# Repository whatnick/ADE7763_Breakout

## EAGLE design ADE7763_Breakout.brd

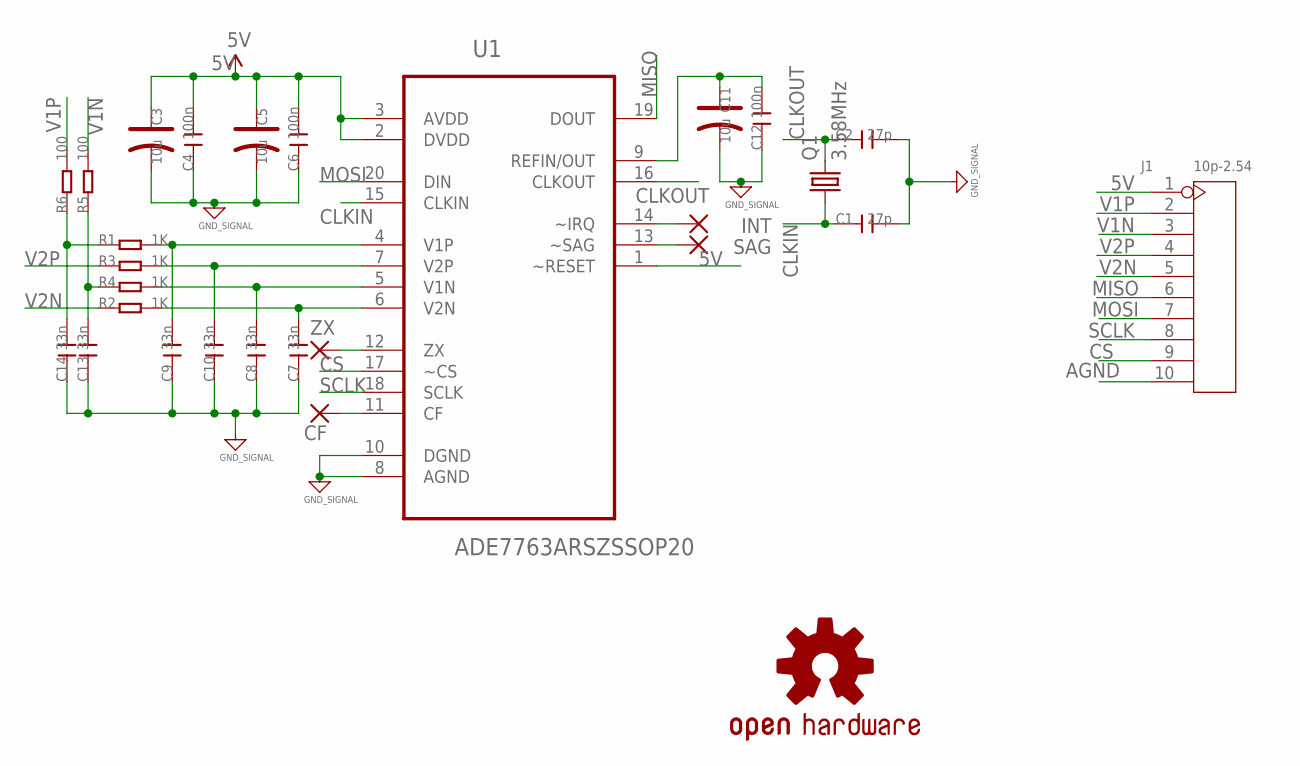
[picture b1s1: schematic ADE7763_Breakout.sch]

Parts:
C1, C2: 27p; C0603
C3, C5, C11: 10u; AVX-A
C4, C6, C12: 100n; C0603
C7, C8, C9, C10, C13, C14: 33n; C0603
CF: WIREPADSMD1,27-254; SMD1,27-2,54
INT: WIREPADSMD1,27-254; SMD1,27-2,54
J1: 10p-2.54; H10-2.54
LOGO1: OSHW-LOGOM; OSHW-LOGO-M
Q1: 3.58MHz; HC49UP
R1, R2, R3, R4: 1K; R0603
R5, R6: 100; R0603
SAG: WIREPADSMD1,27-254; SMD1,27-2,54
U1: ADE7763ARSZSSOP20; RS_20-M
ZX: WIREPADSMD1,27-254; SMD1,27-2,54

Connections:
5V: C3.+, C4.2, C5.+, C6.2, J1.1, U1.1 (~RESET), U1.2 (DVDD), U1.3 (AVDD)
AGND: C1.2, C2.2, C3.-, C4.1, C5.-, C6.1, C7.1, C8.1, C9.1, C10.1, C11.-, C12.1, C13.1, C14.1, J1.10, U1.8 (AGND), U1.10 (DGND)
CLKIN: C1.1, Q1.1, U1.15 (CLKIN)
CLKOUT: C2.1, Q1.2, U1.16 (CLKOUT)
CS: J1.9, U1.17 (~CS)
MISO: J1.6, U1.19 (DOUT)
MOSI: J1.7, U1.20 (DIN)
unnamed: C13.2, R4.1, R5.1
unnamed: C14.2, R1.1, R6.1
unnamed: INT.1, U1.14 (~IRQ)
unnamed: C7.2, R2.2, U1.6 (V2N)
unnamed: C8.2, R4.2, U1.5 (V1N)
unnamed: C10.2, R3.2, U1.7 (V2P)
unnamed: C9.2, R1.2, U1.4 (V1P)
unnamed: SAG.1, U1.13 (~SAG)
unnamed: C11.+, C12.2, U1.9 (REFIN/OUT)
unnamed: U1.12 (ZX), ZX.1
unnamed: CF.1, U1.11 (CF)
SCLK: J1.8, U1.18 (SCLK)
V1N: J1.3, R5.2
V1P: J1.2, R6.2
V2N: J1.5, R2.1
V2P: J1.4, R3.1

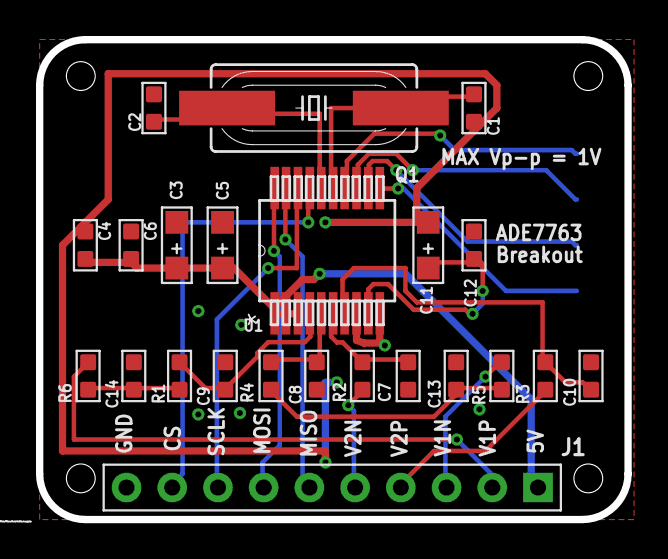
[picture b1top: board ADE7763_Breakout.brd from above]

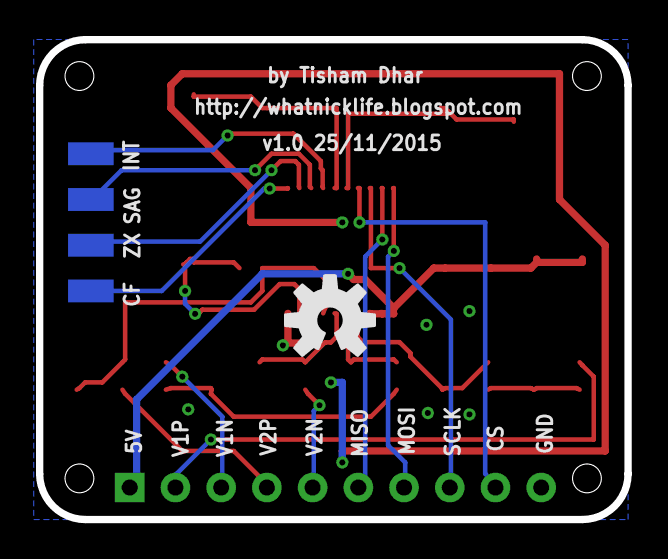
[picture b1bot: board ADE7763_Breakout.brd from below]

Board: 2 copper layers, 32.7 x 26.7 mm, 28 parts (5 on the bottom side), 23 nets.

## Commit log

2015-10-27 Initial import
2015-10-27 Bigger drills
2015-11-25 Corrected footprint and labels, added wirepads for other pins

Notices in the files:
parts and their libraries:
SparkFun-Aesthetics: Licensing: Creative Commons ShareAlike 4.0 International - https://creativecommons.org/licenses/by-sa/4.0
